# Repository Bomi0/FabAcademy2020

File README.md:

# FabAcademy2020
FabAcademy 2020's shared file repository

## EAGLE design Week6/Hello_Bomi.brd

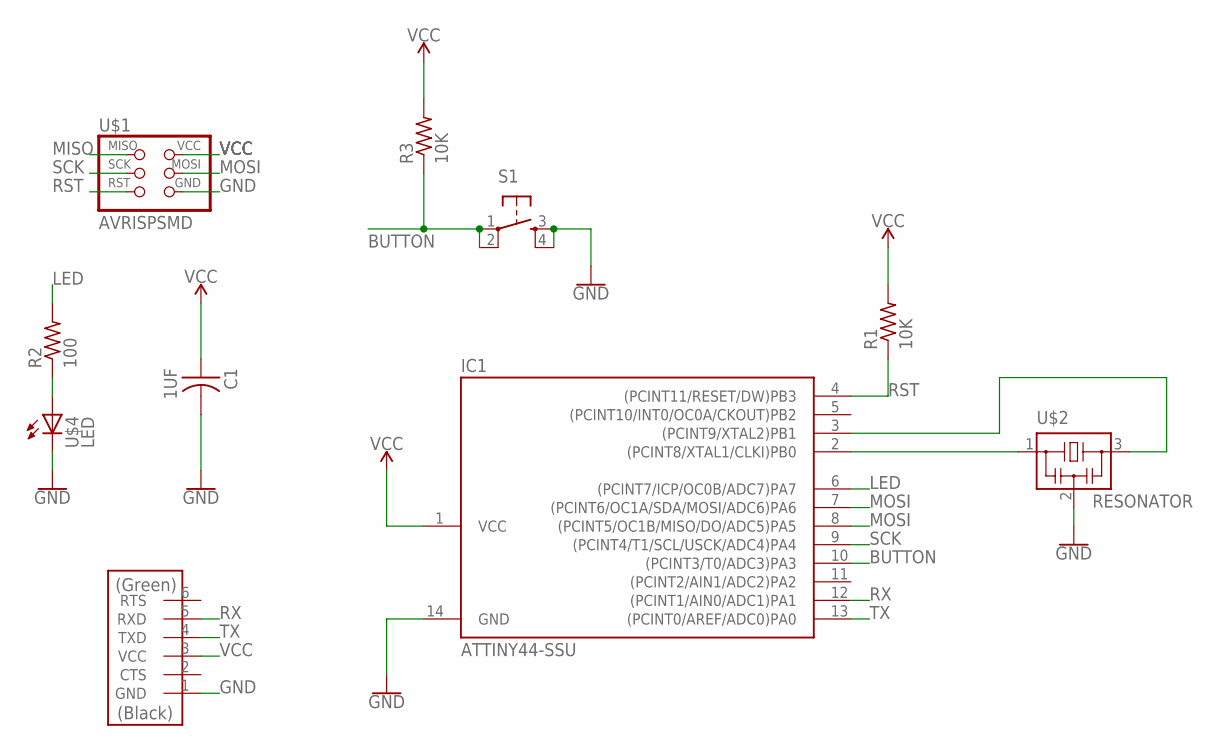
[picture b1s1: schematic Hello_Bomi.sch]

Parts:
C1: 1UF; C1206FAB
IC1: ATTINY44-SSU; SOIC14
R1, R3: 10K; R1206FAB
R2: 100; R1206FAB
S1: 6MM_SWITCH6MM_SWITCH; 6MM_SWITCH
U$1: AVRISPSMD; 2X03SMD
U$2: RESONATOR; EFOBM
U$3: FTDI-SMD-HEADER; 1X06SMD
U$4: LED; LED1206FAB

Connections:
BUTTON: IC1.10 ((PCINT3/T0/ADC3)PA3), R3.1, S1.1, S1.2 (P1)
GND: C1.2, IC1.14 (GND), S1.3 (S), S1.4 (S1), U$1.6 (GND), U$2.2, U$3.1 (GND), U$4.2 (C)
LED: IC1.6 ((PCINT7/ICP/OC0B/ADC7)PA7), R2.2
MISO: U$1.1 (MISO)
MOSI: IC1.7 ((PCINT6/OC1A/SDA/MOSI/ADC6)PA6), IC1.8 ((PCINT5/OC1B/MISO/DO/ADC5)PA5), U$1.4 (MOSI)
unnamed: R2.1, U$4.1 (A)
unnamed: IC1.2 ((PCINT8/XTAL1/CLKI)PB0), U$2.1
unnamed: IC1.3 ((PCINT9/XTAL2)PB1), U$2.3
RST: IC1.4 ((PCINT11/RESET/DW)PB3), R1.1, U$1.5 (RST)
RX: IC1.12 ((PCINT1/AIN0/ADC1)PA1), U$3.5 (RXD)
SCK: IC1.9 ((PCINT4/T1/SCL/USCK/ADC4)PA4), U$1.3 (SCK)
TX: IC1.13 ((PCINT0/AREF/ADC0)PA0), U$3.4 (TXD)
VCC: C1.1, IC1.1 (VCC), R1.2, R3.2, U$1.2 (VCC), U$3.3 (VCC)

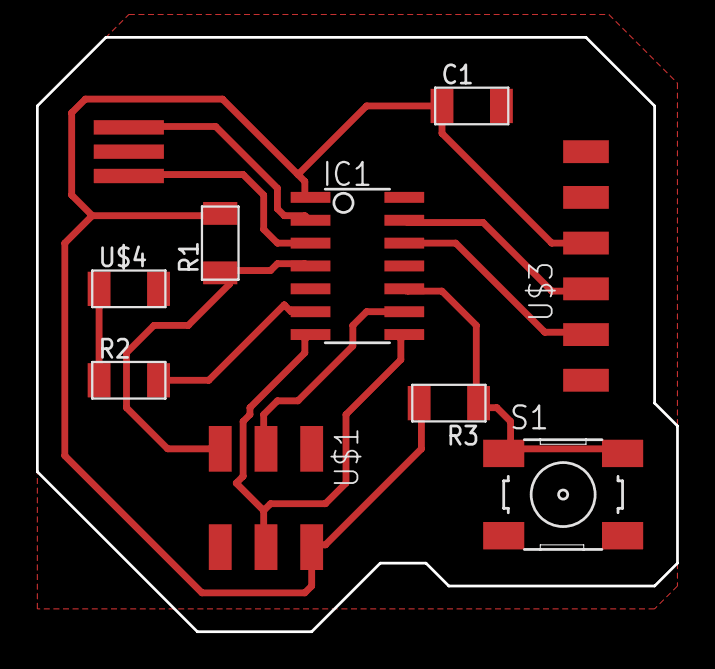
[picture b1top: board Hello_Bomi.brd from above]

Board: 2 copper layers, 35.6 x 33.0 mm, 10 parts (0 on the bottom side), 12 nets.

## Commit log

2020-03-17 0317

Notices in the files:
parts and their libraries:
SparkFun-PowerSymbols: Licensing: Creative Commons ShareAlike 4.0 International - https://creativecommons.org/licenses/by-sa/4.0
